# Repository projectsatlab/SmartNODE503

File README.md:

# SmartezNODE503
Smart ezNODE 503 hardware and software platform.

Hardware design assembly into 503 electric plant box based on ESP8266-012F WIFI module. 

Software architecture designed to interface TINKER MODE IoT devices platform.

Coming soon...

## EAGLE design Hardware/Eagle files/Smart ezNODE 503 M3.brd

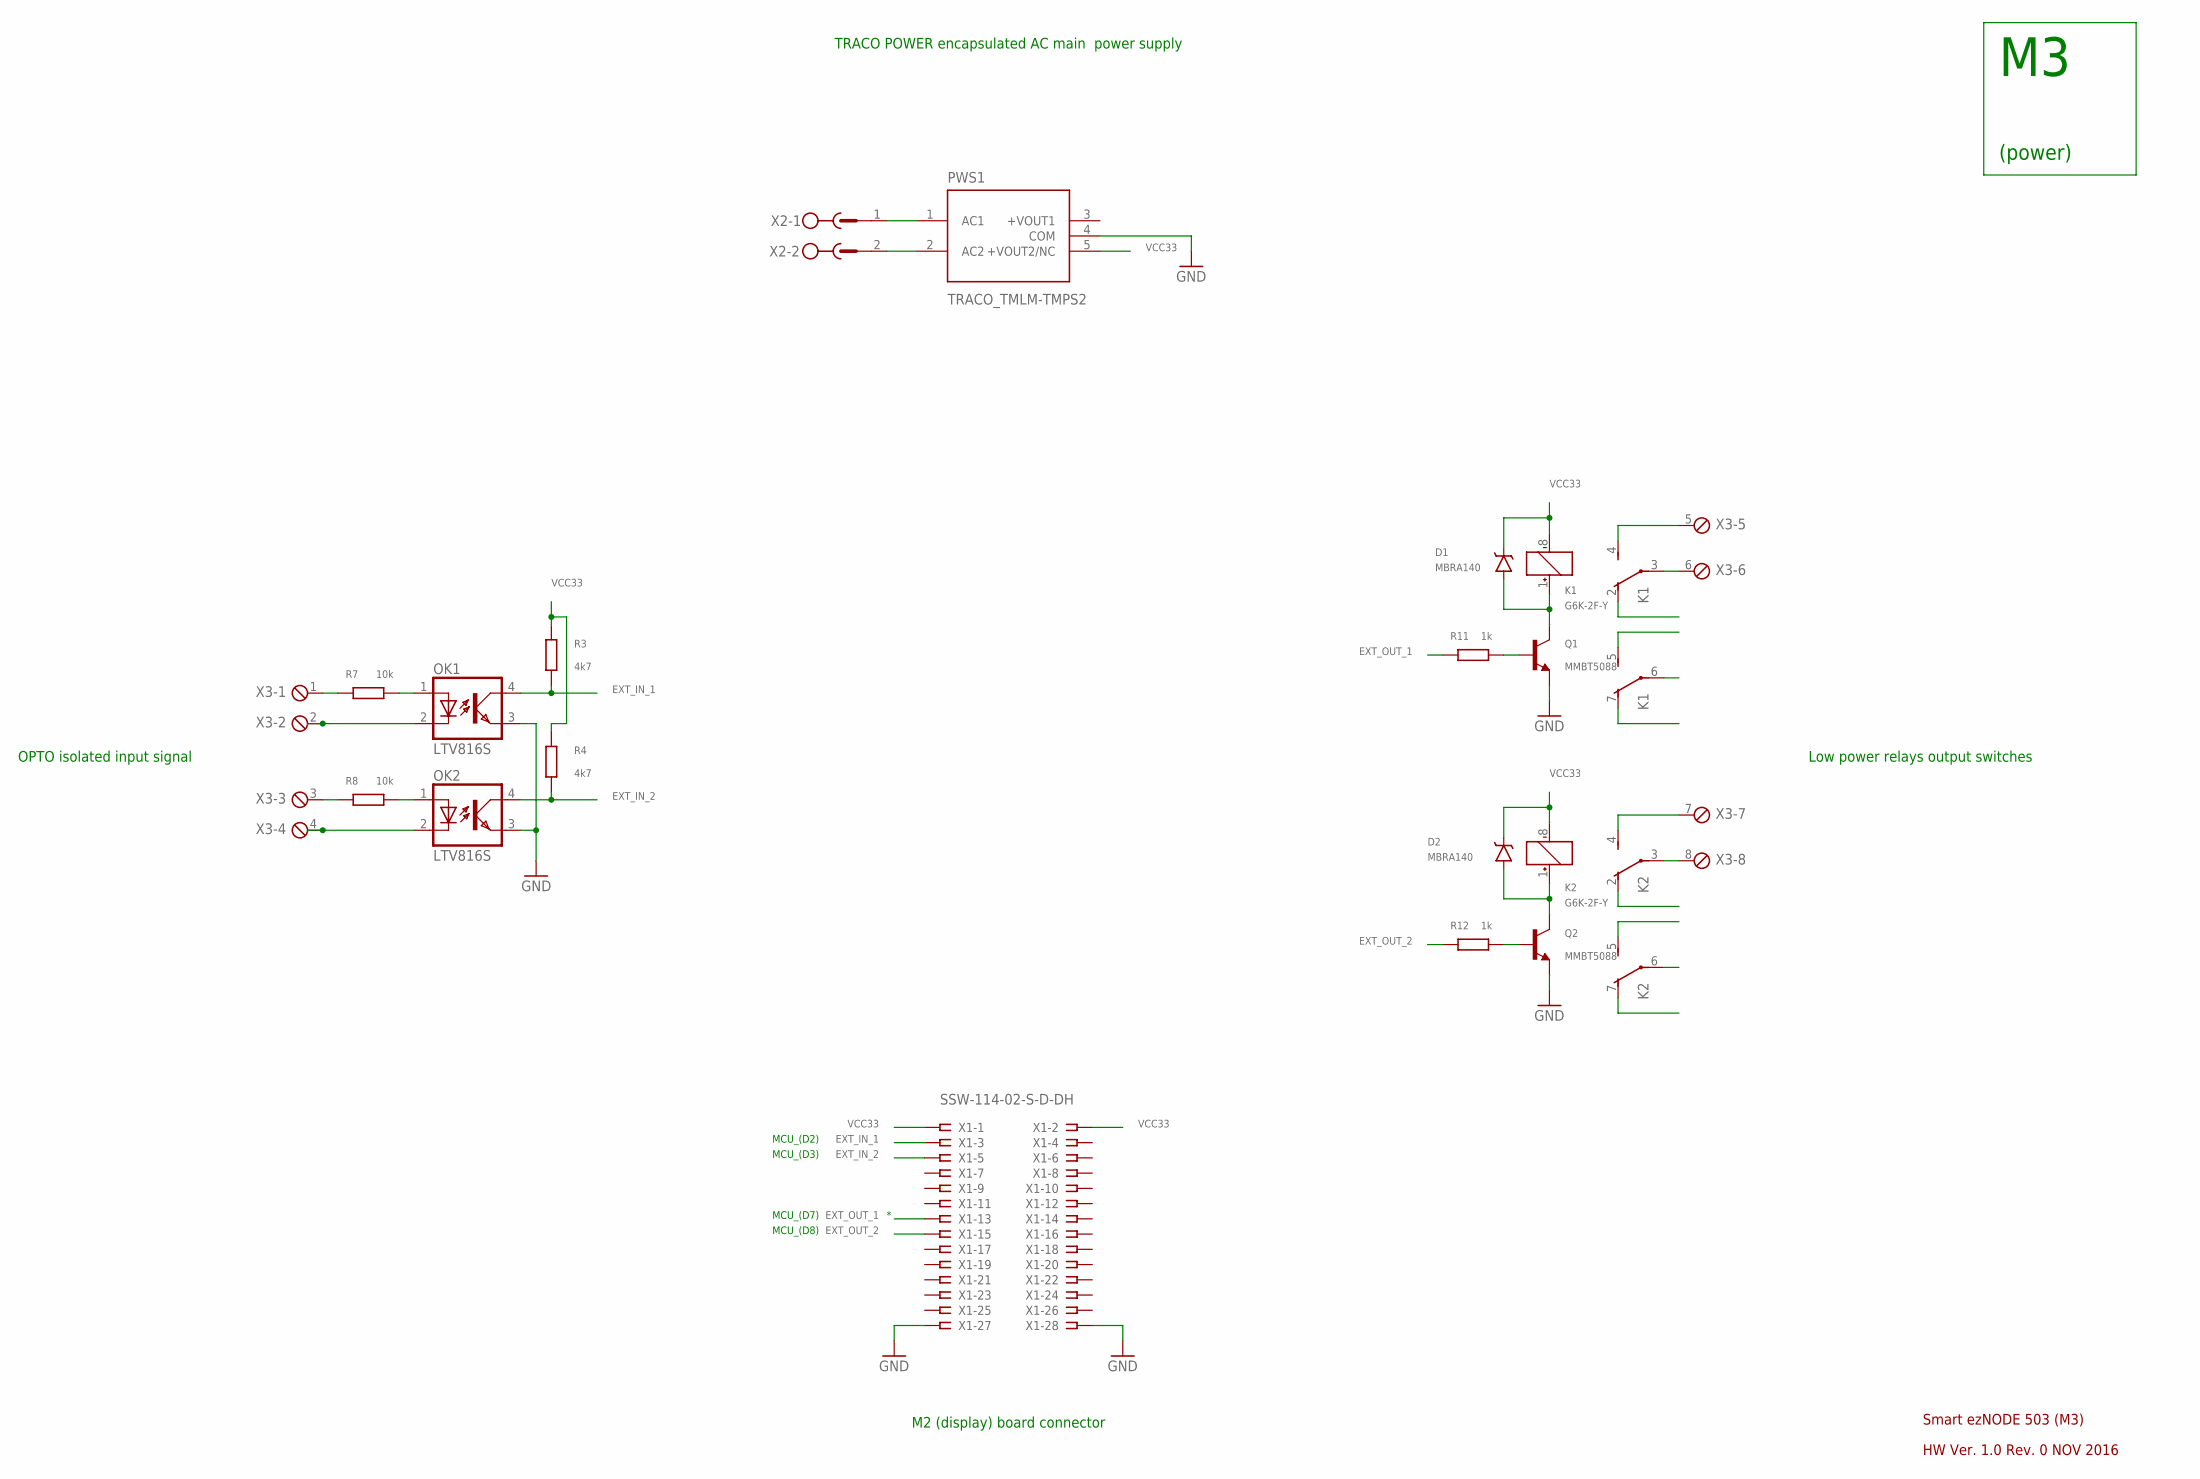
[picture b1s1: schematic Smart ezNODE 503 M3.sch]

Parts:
D1, D2: MBRA140; SMA-DIODE
K1, K2: G6K-2F-Y
OK1, OK2: LTV816S; SMD4
PWS1: TRACO_TMLM-TMPS2; TRACO_TMPS03XXX
Q1, Q2: MMBT5088; SOT23-3
R3, R4: 4k7; R0402
R7, R8: 10k; R0402
R11, R12: 1k; R0402
X1: SSW-114-02-S-D-DH; FTE-114-XX-G-DH
X2: MSTBV2
X3: MPT8; 8POL254

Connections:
EXT_IN_1: OK1.4 (COL), R3.1, X1.3
EXT_IN_2: OK2.4 (COL), R4.1, X1.5
EXT_OUT_1: R11.1, X1.13
EXT_OUT_2: R12.1, X1.15
GND: OK1.3 (EMIT), OK2.3 (EMIT), PWS1.4 (COM), Q1.2 (E), Q2.2 (E), X1.27, X1.28
unnamed: PWS1.1 (AC1), X2.1
unnamed: PWS1.2 (AC2), X2.2
unnamed: R7.1, X3.1
unnamed: R8.1, X3.3
unnamed: K1.4 (S), X3.5
unnamed: OK1.2 (C), X3.2
unnamed: OK1.1 (A), R7.2
unnamed: OK2.1 (A), R8.2
unnamed: OK2.2 (C), X3.4
unnamed: K1.3, X3.6
unnamed: D1.A, K1.1 (+), Q1.3 (C)
unnamed: D2.A, K2.1 (+), Q2.3 (C)
unnamed: Q1.1 (B), R11.2
unnamed: Q2.1 (B), R12.2
unnamed: K2.4 (S), X3.7
unnamed: K2.3, X3.8
VCC33: D1.C, D2.C, K1.8 (-), K2.8 (-), PWS1.5 (+VOUT2/NC), R3.2, R4.2, X1.1, X1.2

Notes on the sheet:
(power)
Smart ezNODE 503 (M3)
HW Ver. 1.0 Rev. 0 NOV 2016
TRACO POWER encapsulated AC main power supply
MCU_(D2)
MCU_(D3)
MCU_(D7)
MCU_(D8)
OPTO isolated input signal
Low power relays output switches
M2 (display) board connector

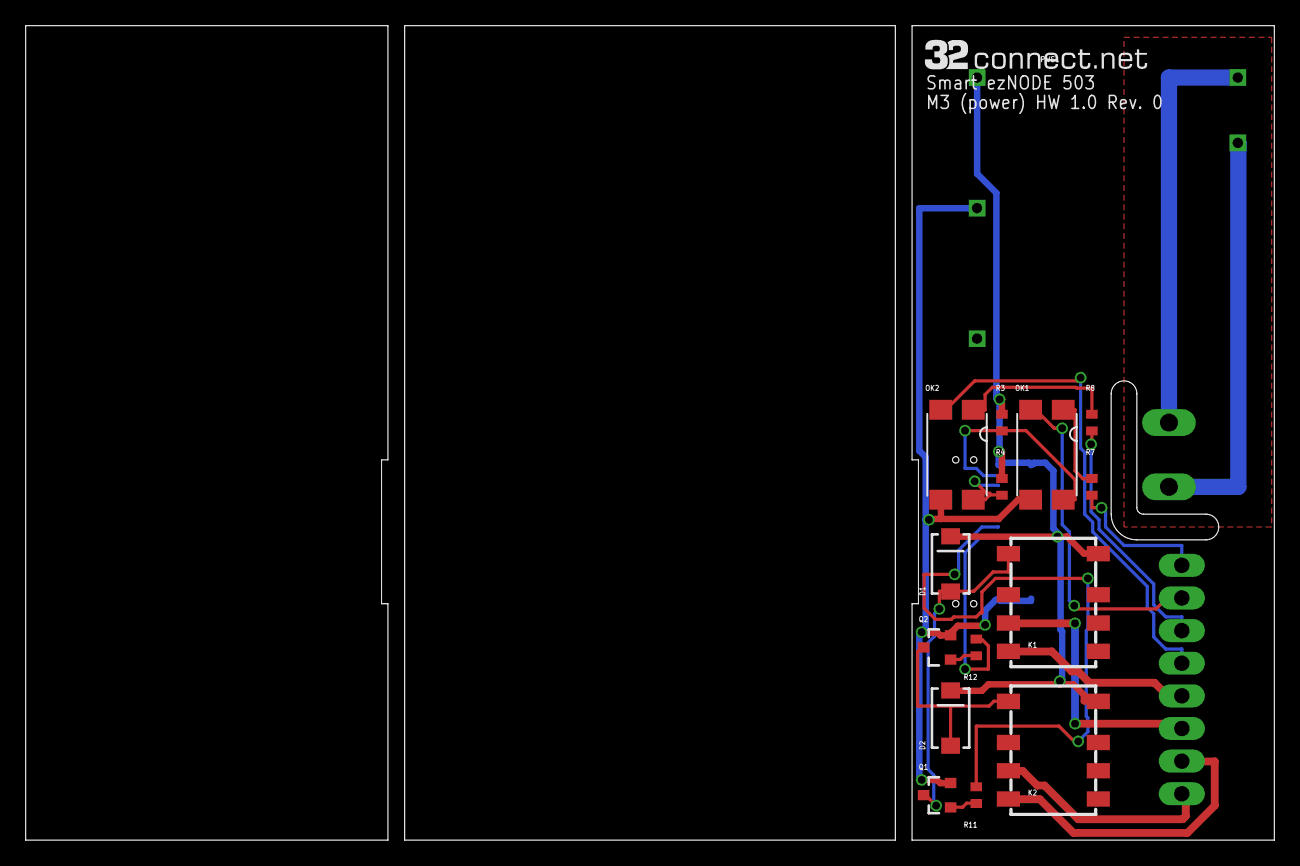
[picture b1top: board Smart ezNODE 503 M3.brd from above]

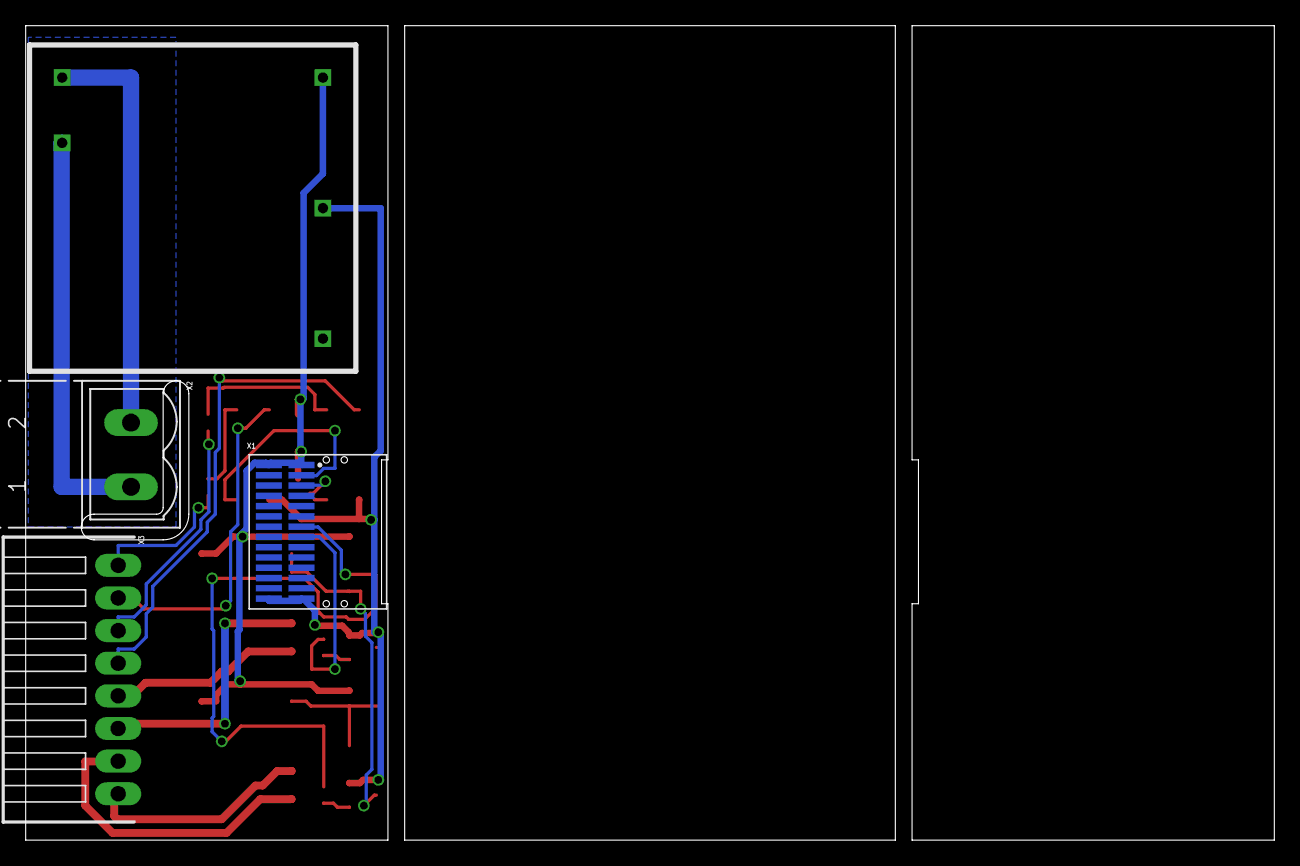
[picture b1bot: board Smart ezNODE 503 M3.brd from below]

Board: 2 copper layers, 97.2 x 63.4 mm, 18 parts (4 on the bottom side), 22 nets.

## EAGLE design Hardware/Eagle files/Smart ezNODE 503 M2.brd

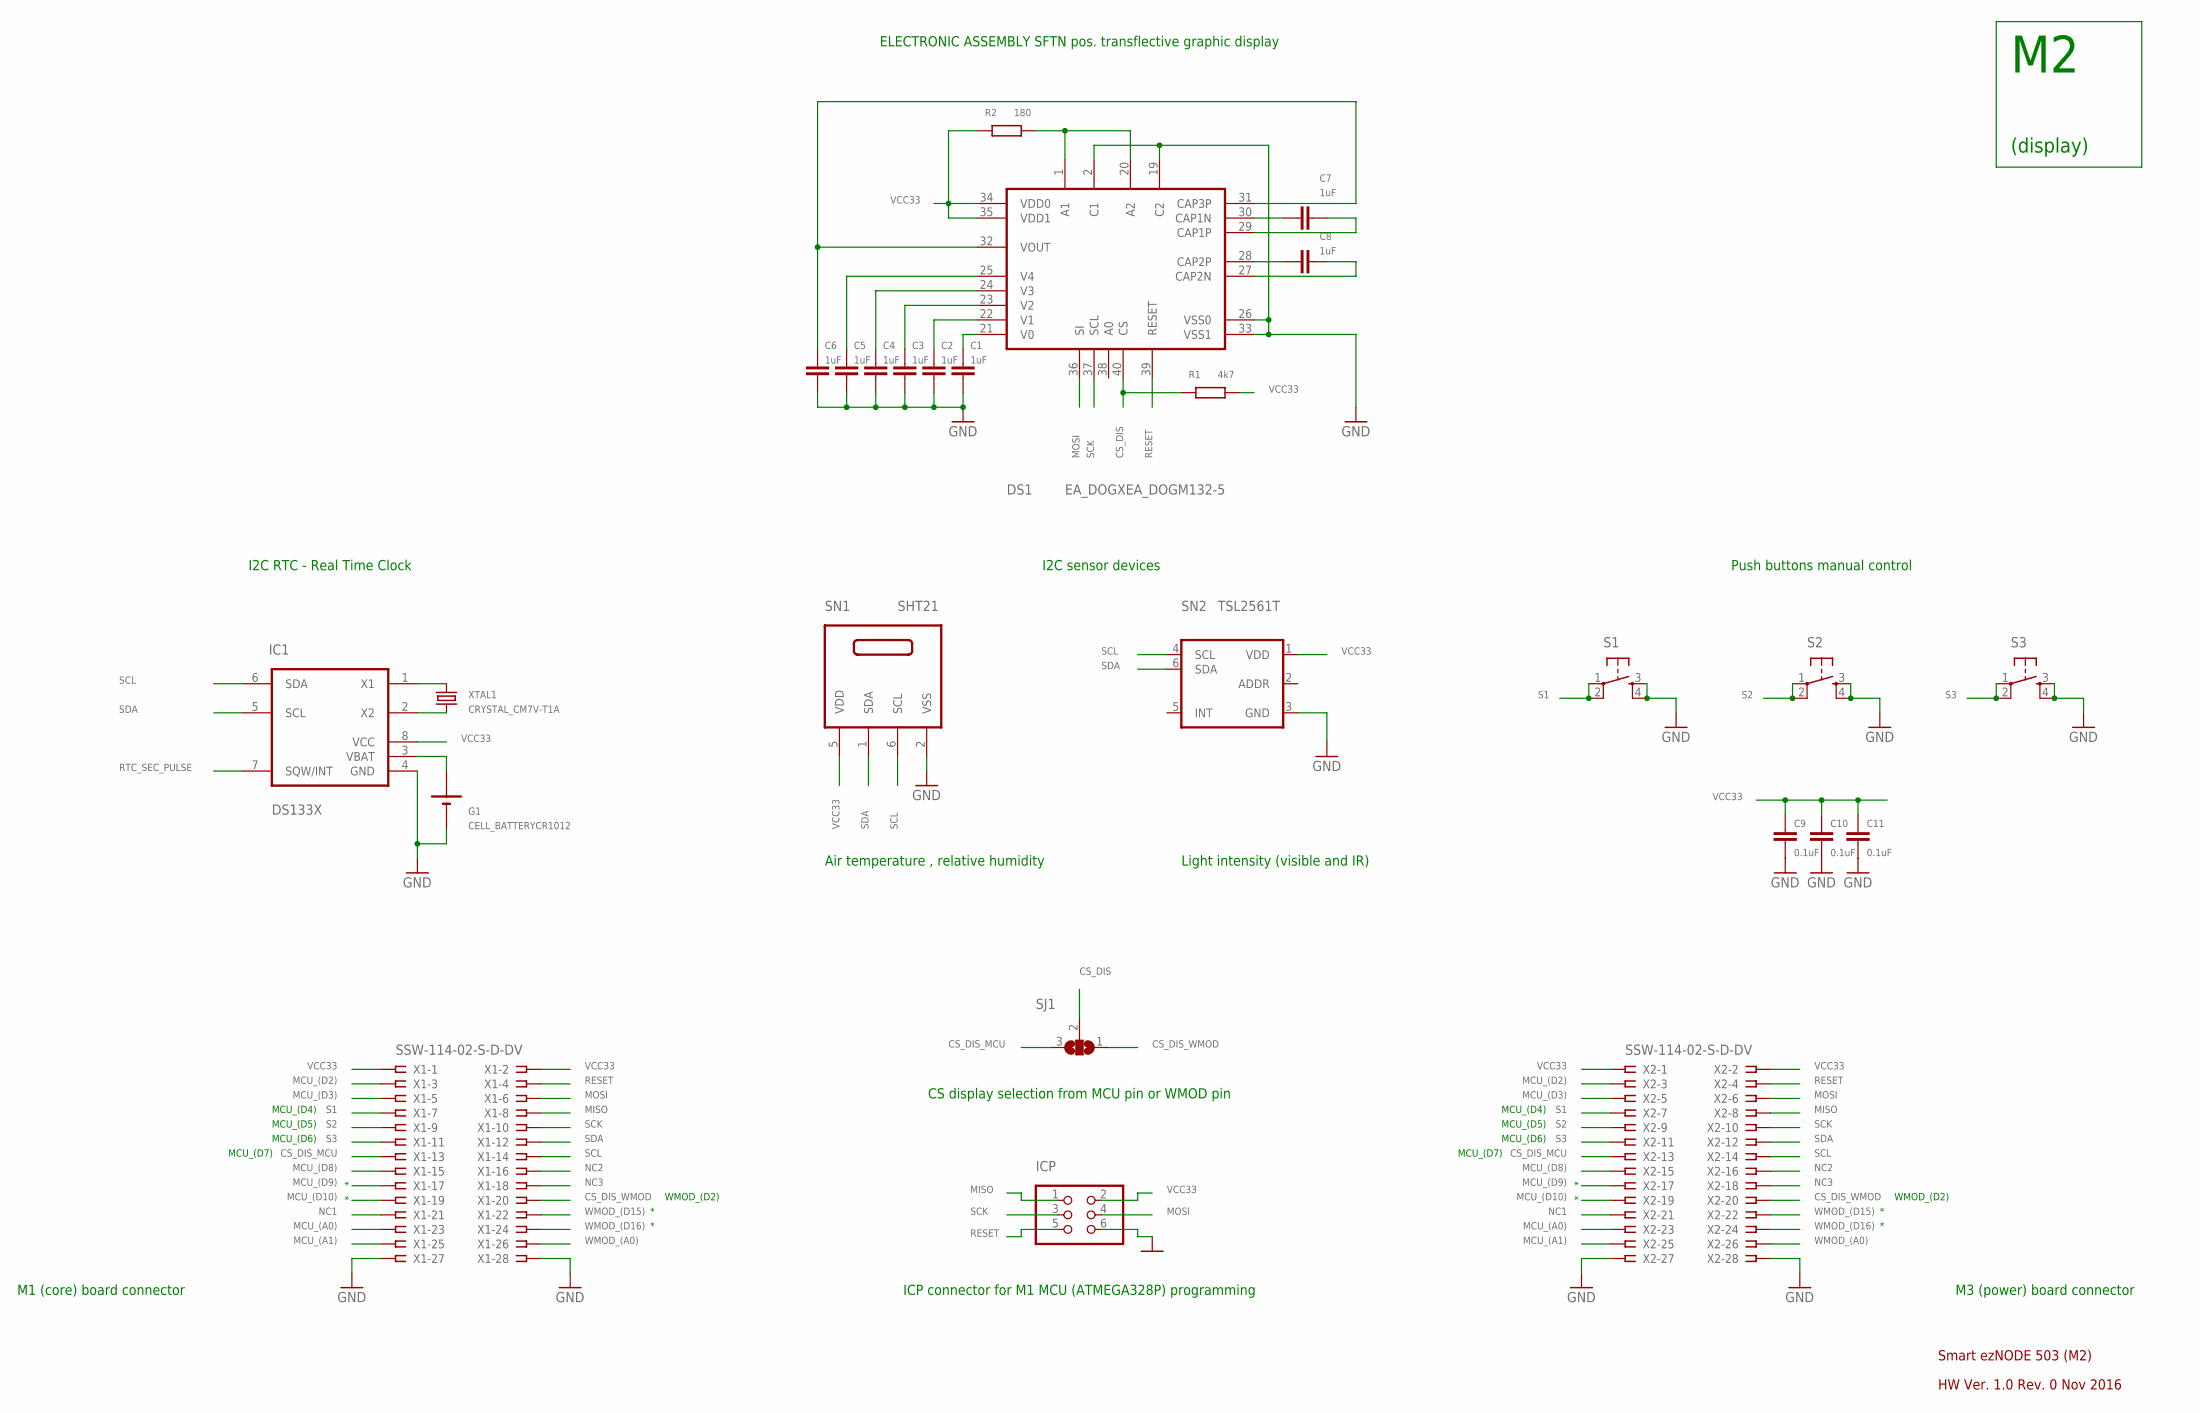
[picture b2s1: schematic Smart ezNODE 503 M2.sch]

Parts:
C1, C2, C3, C4, C5, C6, C7, C8: 1uF; C0402
C9, C10, C11: 0.1uF; C0402
DS1: EA_DOGXEA_DOGM132-5; EA_DOGM
G1: CELL_BATTERYCR1012; 12MM_SMD_COIN_CELL_BATTERY_HOLDER
IC1: DS133X; MICRO08
ICP: PINHD-2X3/SMD; 2X3_SMD
R1: 4k7; R0402
R2: 180; R0805
S1, S2, S3: TAC_SWITCH3; C&KKSCX_BEND
SJ1: SJ2W; SJ_2
SN1: SHT21; DFN6/SHT
SN2: TSL2561T; TMB-6
X1, X2: SSW-114-02-S-D-DV; CLE-114-01-X-DV-A
XTAL1: CRYSTAL_CM7V-T1A

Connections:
CS_DIS: DS1.40 (CS), R1.1, SJ1.2
CS_DIS_MCU: SJ1.3, X1.13, X2.13
CS_DIS_WMOD: SJ1.1, X1.20, X2.20
GND: C1.2, C2.2, C3.2, C4.2, C5.2, C6.2, C9.2, C10.2, C11.2, DS1.2 (C1), DS1.19 (C2), DS1.26 (VSS0), DS1.33 (VSS1), G1.P$2 (-), IC1.4 (GND), ICP.6, S1.3, S1.4, S2.3, S2.4, S3.3, S3.4, SN1.2 (VSS), SN2.3 (GND), X1.27, X1.28, X2.27, X2.28
MCU_(A0): X1.23, X2.23
MCU_(A1): X1.25, X2.25
MCU_(D2): X1.3, X2.3
MCU_(D3): X1.5, X2.5
MCU_(D8): X1.15, X2.15
MCU_(D9): X1.17, X2.17
MCU_(D10): X1.19, X2.19
MISO: ICP.1, X1.8, X2.8
MOSI: DS1.36 (SI), ICP.4, X1.6, X2.6
unnamed: IC1.1 (X1), XTAL1.P$2 (2)
unnamed: IC1.2 (X2), XTAL1.P$1 (1)
unnamed: DS1.1 (A1), DS1.20 (A2), R2.1
unnamed: C1.1, DS1.21 (V0)
unnamed: C7.1, DS1.30 (CAP1N)
unnamed: C2.1, DS1.22 (V1)
unnamed: C3.1, DS1.23 (V2)
unnamed: C4.1, DS1.24 (V3)
unnamed: C5.1, DS1.25 (V4)
unnamed: C6.1, DS1.31 (CAP3P), DS1.32 (VOUT)
unnamed: C7.2, DS1.29 (CAP1P)
unnamed: C8.1, DS1.28 (CAP2P)
unnamed: C8.2, DS1.27 (CAP2N)
unnamed: G1.P$1 (+), IC1.3 (VBAT)
NC1: X1.21, X2.21
NC2: X1.16, X2.16
NC3: X1.18, X2.18
RESET: DS1.39 (RESET), ICP.5, X1.4, X2.4
RTC_SEC_PULSE: IC1.7 (SQW/INT)
S1: S1.1, S1.2, X1.7, X2.7
S2: S2.1, S2.2, X1.9, X2.9
S3: S3.1, S3.2, X1.11, X2.11
SCK: DS1.37 (SCL), ICP.3, X1.10, X2.10
SCL: IC1.5 (SCL), SN1.6 (SCL), SN2.4 (SCL), X1.14, X2.14
SDA: IC1.6 (SDA), SN1.1 (SDA), SN2.6 (SDA), X1.12, X2.12
VCC33: C9.1, C10.1, C11.1, DS1.34 (VDD0), DS1.35 (VDD1), IC1.8 (VCC), ICP.2, R1.2, R2.2, SN1.5 (VDD), SN2.1 (VDD), X1.1, X1.2, X2.1, X2.2
WMOD_(A0): X1.26, X2.26
WMOD_(D15): X1.22, X2.22
WMOD_(D16): X1.24, X2.24

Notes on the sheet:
(display)
Smart ezNODE 503 (M2)
HW Ver. 1.0 Rev. 0 Nov 2016
WMOD_(D2)
MCU_(D4)
MCU_(D5)
MCU_(D6)
ELECTRONIC ASSEMBLY SFTN pos. transflective graphic display
I2C sensor devices
Air temperature , relative humidity
Light intensity (visible and IR)
I2C RTC - Real Time Clock
ICP connector for M1 MCU (ATMEGA328P) programming
M1 (core) board connector
M3 (power) board connector
Push buttons manual control
MCU_(D7)
CS display selection from MCU pin or WMOD pin

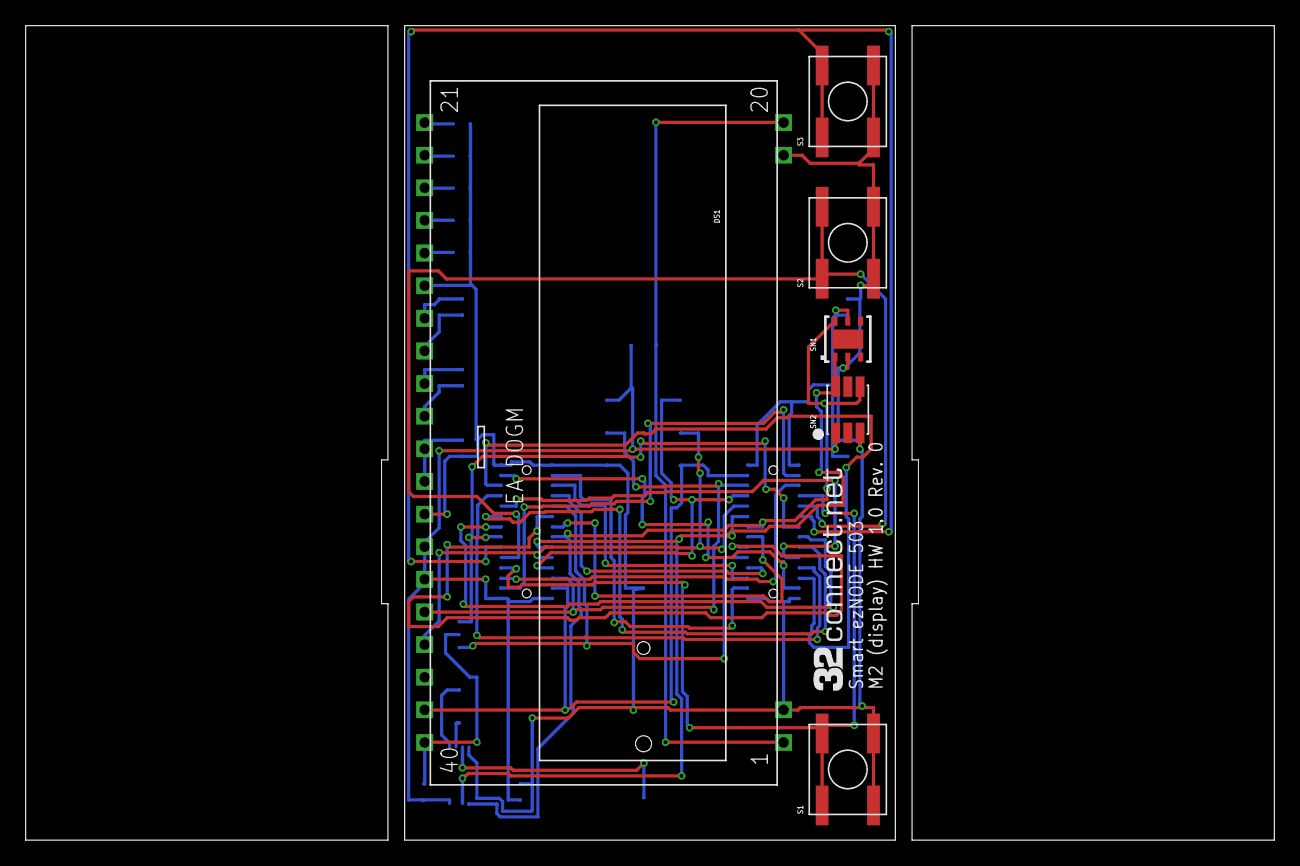
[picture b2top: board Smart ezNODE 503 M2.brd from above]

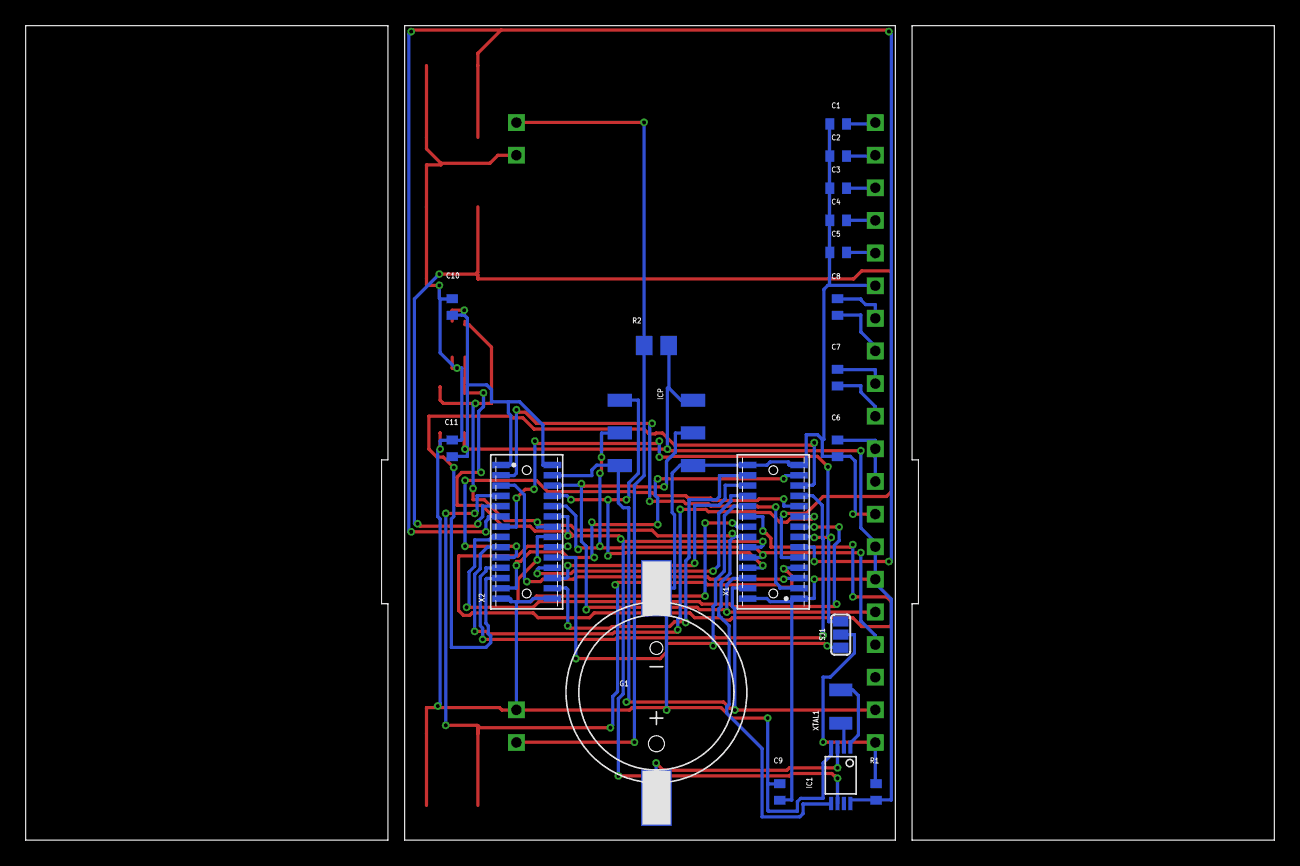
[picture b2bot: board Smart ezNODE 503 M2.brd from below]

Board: 2 copper layers, 97.2 x 63.4 mm, 26 parts (20 on the bottom side), 41 nets.

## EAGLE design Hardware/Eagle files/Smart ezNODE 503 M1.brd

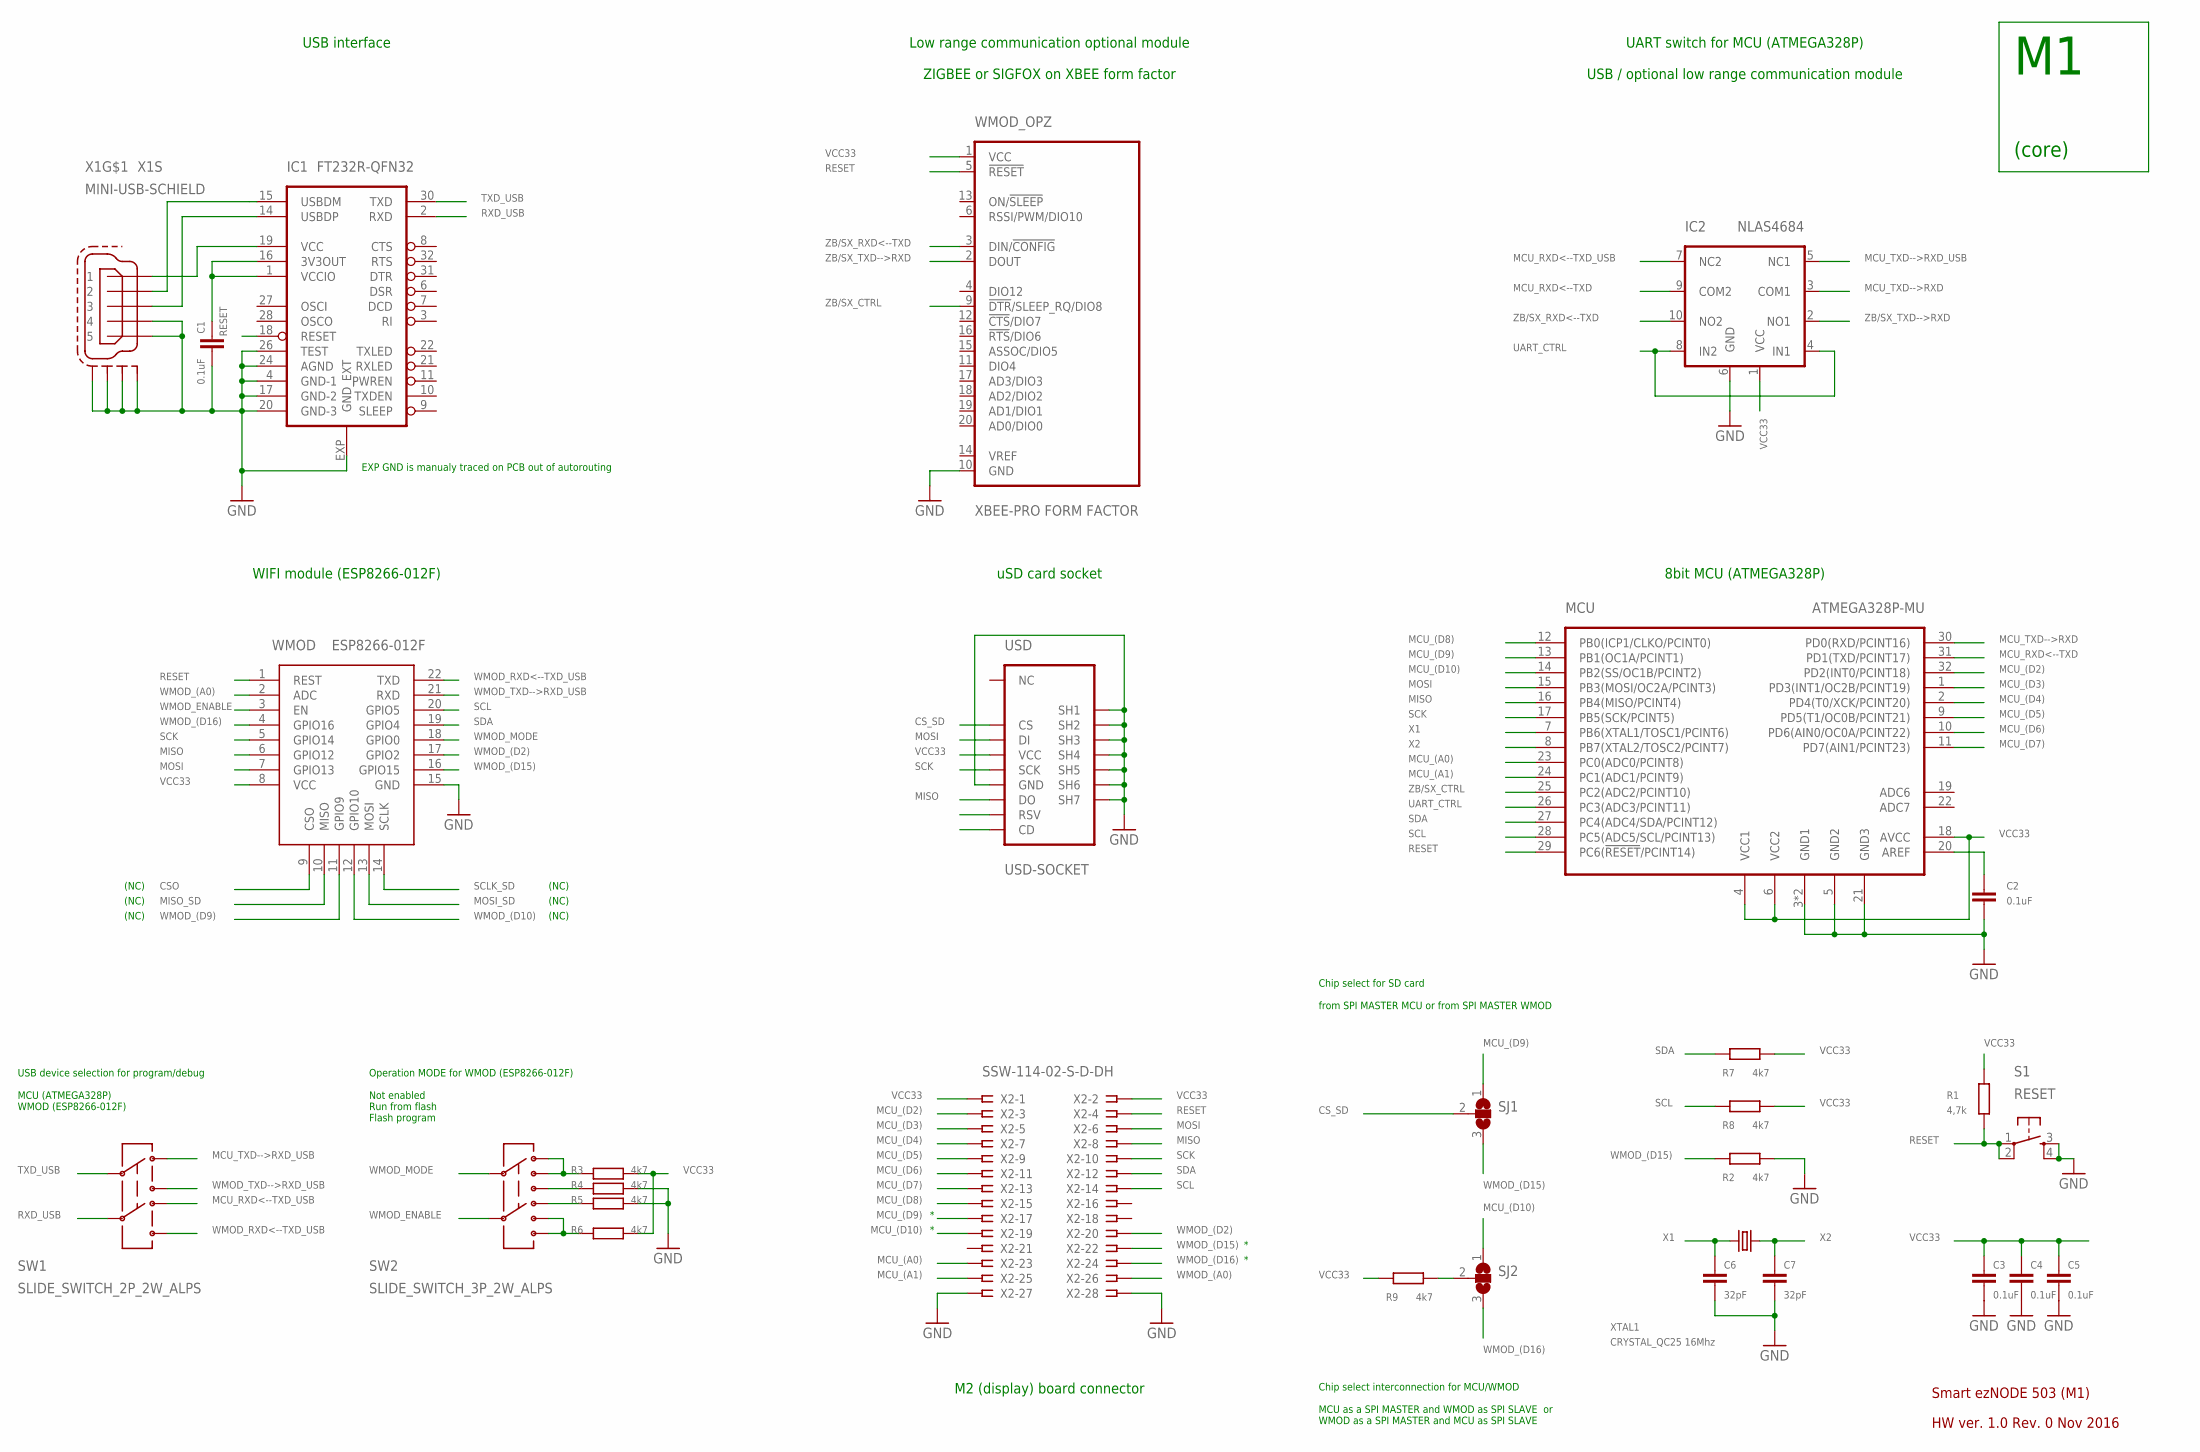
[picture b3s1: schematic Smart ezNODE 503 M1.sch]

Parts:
C1, C2, C3, C4, C5: 0.1uF; C0402
C6, C7: 32pF; C0201
IC1: FT232R-QFN32; QFN32
IC2: NLAS4684; MSOP10
MCU: ATMEGA328P-MU; MLF32
R1: 4,7k; R0402
R2, R3, R4, R5, R6, R7, R8, R9: 4k7; R0402
S1: RESET; C&K_KMS
SJ1, SJ2: SJ2W; SJ_2
SW1: SLIDE_SWITCH_2P_2W_ALPS; SLIDE_SWITCH_ALPS_SSSS820201
SW2: SLIDE_SWITCH_3P_2W_ALPS; SLIDE_SWITCH_ALPS_SSSS820301
USD: USD-SOCKET; USD-SOCKET-PP
WMOD: ESP8266-012F; ESP8266-ESP12
WMOD_OPZ: XBEE-PRO FORM FACTOR; XBEE-PRO
X1: MINI-USB-SCHIELD; MOLEX_67503-X20
X2: SSW-114-02-S-D-DH; FTE-114-XX-G-DH
XTAL1: CRYSTAL_QC25 16Mhz; CRYSTAL_QC25

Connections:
CSO: WMOD.9 (CSO)
CS_SD: SJ1.2, USD.P$2 (CS)
D+: IC1.14 (USBDP), X1.3
D-: IC1.15 (USBDM), X1.2
GND: C1.2, C2.2, C3.2, C4.2, C5.2, C6.2, C7.2, IC1.4 (GND-1), IC1.17 (GND-2), IC1.20 (GND-3), IC1.24 (AGND), IC1.26 (TEST), IC1.EXP (GND_EXT), IC2.6 (GND), MCU.3 (GND1), MCU.5 (GND2), MCU.21 (GND3), MCU.TH (GND1), R2.2, R4.1, R5.1, S1.3, S1.4, USD.P$6 (GND), USD.P$9 (SH1), USD.P$10 (SH2), USD.P$12 (SH3), USD.P$13 (SH4), USD.P$14 (SH5), USD.P$15 (SH6), USD.P$16 (SH7), WMOD.15 (GND), WMOD_OPZ.10 (GND), X1.4, X1.5, X1.M1 (S1), X1.M2 (S2), X1.M3 (S3), X1.M4 (S4), X2.27, X2.28
MCU_(A0): MCU.23 (PC0(ADC0/PCINT8)), X2.23
MCU_(A1): MCU.24 (PC1(ADC1/PCINT9)), X2.25
MCU_(D2): MCU.32 (PD2(INT0/PCINT18)), X2.3
MCU_(D3): MCU.1 (PD3(INT1/OC2B/PCINT19)), X2.5
MCU_(D4): MCU.2 (PD4(T0/XCK/PCINT20)), X2.7
MCU_(D5): MCU.9 (PD5(T1/OC0B/PCINT21)), X2.9
MCU_(D6): MCU.10 (PD6(AIN0/OC0A/PCINT22)), X2.11
MCU_(D7): MCU.11 (PD7(AIN1/PCINT23)), X2.13
MCU_(D8): MCU.12 (PB0(ICP1/CLKO/PCINT0)), X2.15
MCU_(D9): MCU.13 (PB1(OC1A/PCINT1)), SJ1.1, X2.17
MCU_(D10): MCU.14 (PB2(SS/OC1B/PCINT2)), SJ2.1, X2.19
MCU_RXD<--TXD: IC2.9 (COM2), MCU.31 (PD1(TXD/PCINT17))
MCU_RXD<--TXD_USB: IC2.7 (NC2), SW1.4
MCU_TXD-->RXD: IC2.3 (COM1), MCU.30 (PD0(RXD/PCINT16))
MCU_TXD-->RXD_USB: IC2.5 (NC1), SW1.1
MISO: MCU.16 (PB4(MISO/PCINT4)), USD.P$7 (DO), WMOD.6 (GPIO12), X2.8
MISO_SD: WMOD.10 (MISO)
MOSI: MCU.15 (PB3(MOSI/OC2A/PCINT3)), USD.P$3 (DI), WMOD.7 (GPIO13), X2.6
MOSI_SD: WMOD.13 (MOSI)
unnamed: R9.2, SJ2.2
unnamed: C1.1, IC1.1 (VCCIO), IC1.16 (3V3OUT)
unnamed: R6.2, SW2.6, SW2.8
unnamed: C2.1, MCU.20 (AREF)
unnamed: R3.2, SW2.1, SW2.2
unnamed: R4.2, SW2.4
unnamed: R5.2, SW2.5
RESET: IC1.18 (RESET), MCU.29 (PC6(!RESET!/PCINT14)), R1.1, S1.1, S1.2, WMOD.1 (REST), WMOD_OPZ.5 (!RESET), X2.4
RXD_USB: IC1.2 (RXD), SW1.5
SCK: MCU.17 (PB5(SCK/PCINT5)), USD.P$5 (SCK), WMOD.5 (GPIO14), X2.10
SCL: MCU.28 (PC5(ADC5/SCL/PCINT13)), R8.1, WMOD.20 (GPIO5), X2.14
SCLK_SD: WMOD.14 (SCLK)
SDA: MCU.27 (PC4(ADC4/SDA/PCINT12)), R7.1, WMOD.19 (GPIO4), X2.12
TXD_USB: IC1.30 (TXD), SW1.2
UART_CTRL: IC2.4 (IN1), IC2.8 (IN2), MCU.26 (PC3(ADC3/PCINT11))
VBUS: IC1.19 (VCC), X1.1
VCC33: C3.1, C4.1, C5.1, IC2.1 (VCC), MCU.4 (VCC1), MCU.6 (VCC2), MCU.18 (AVCC), R1.2, R3.1, R6.1, R7.2, R8.2, R9.1, USD.P$4 (VCC), WMOD.8 (VCC), WMOD_OPZ.1 (VCC), X2.1, X2.2
WMOD_(A0): WMOD.2 (ADC), X2.26
WMOD_(D2): WMOD.17 (GPIO2), X2.20
WMOD_(D9): WMOD.11 (GPIO9)
WMOD_(D10): WMOD.12 (GPIO10)
WMOD_(D15): R2.1, SJ1.3, WMOD.16 (GPIO15), X2.22
WMOD_(D16): SJ2.3, WMOD.4 (GPIO16), X2.24
WMOD_ENABLE: SW2.7, WMOD.3 (EN)
WMOD_MODE: SW2.3, WMOD.18 (GPIO0)
WMOD_RXD<--TXD_USB: SW1.6, WMOD.22 (TXD)
WMOD_TXD-->RXD_USB: SW1.3, WMOD.21 (RXD)
X1: C6.1, MCU.7 (PB6(XTAL1/TOSC1/PCINT6)), XTAL1.P$1 (1)
X2: C7.1, MCU.8 (PB7(XTAL2/TOSC2/PCINT7)), XTAL1.P$3 (3)
ZB/SX_CTRL: MCU.25 (PC2(ADC2/PCINT10)), WMOD_OPZ.9 (!DTR!/SLEEP_RQ/DIO8)
ZB/SX_RXD<--TXD: IC2.10 (NO2), WMOD_OPZ.3 (DIN/!CONFIG)
ZB/SX_TXD-->RXD: IC2.2 (NO1), WMOD_OPZ.2 (DOUT)

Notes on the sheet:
Smart ezNODE 503 (M1)
HW ver. 1.0 Rev. 0 Nov 2016
(core)
Chip select for SD card from SPI MASTER MCU or from SPI MASTER WMOD
Chip select interconnection for MCU/WMOD MCU as a SPI MASTER and WMOD as SPI SLAVE or WMOD as a SPI MASTER and MCU as SPI SLAVE
USB device selection for program/debug MCU (ATMEGA328P) WMOD (ESP8266-012F)
Operation MODE for WMOD (ESP8266-012F) Not enabled Run from flash Flash program
Low range communication optional module ZIGBEE or SIGFOX on XBEE form factor
USB interface
UART switch for MCU (ATMEGA328P) USB / optional low range communication module
WIFI module (ESP8266-012F)
uSD card socket
8bit MCU (ATMEGA328P)
M2 (display) board connector
(NC)
EXP GND is manualy traced on PCB out of autorouting

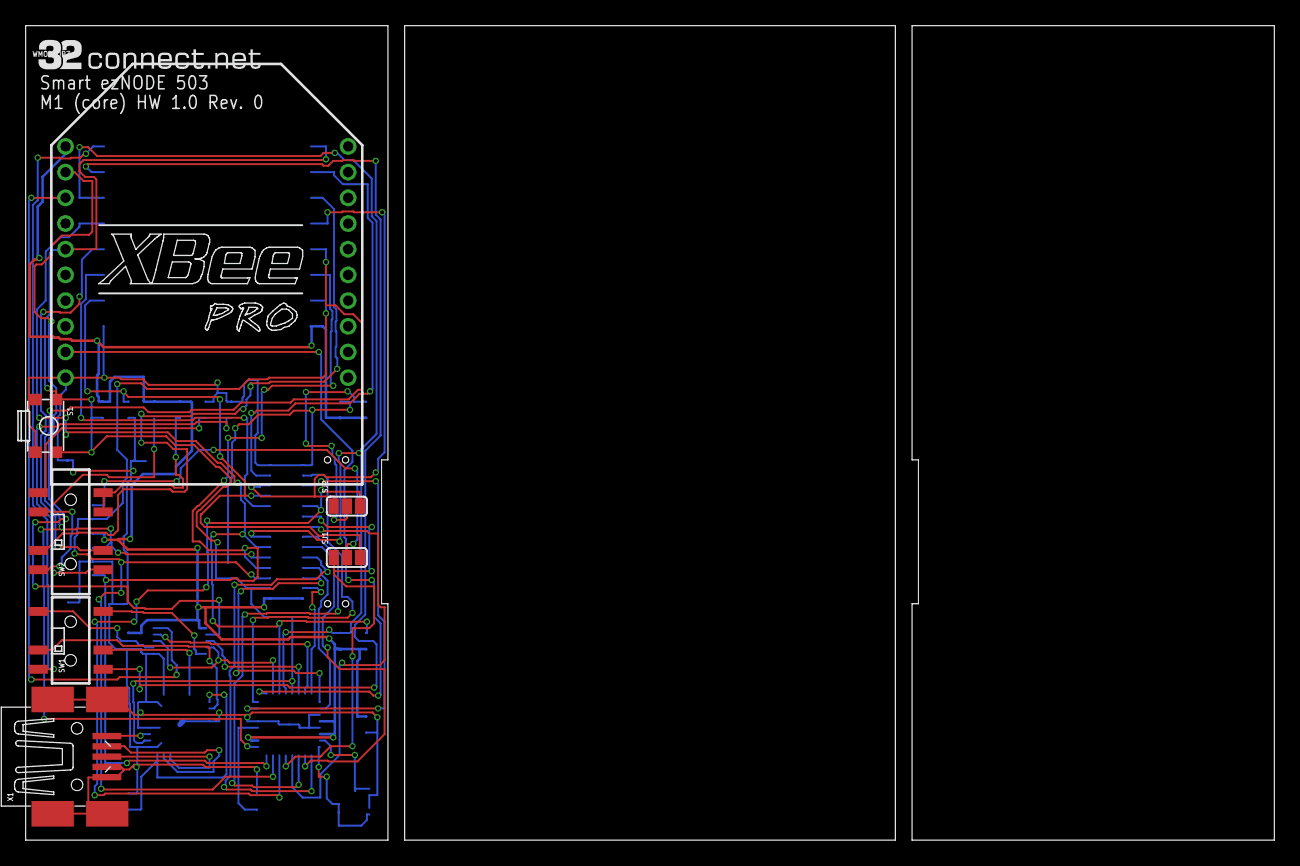
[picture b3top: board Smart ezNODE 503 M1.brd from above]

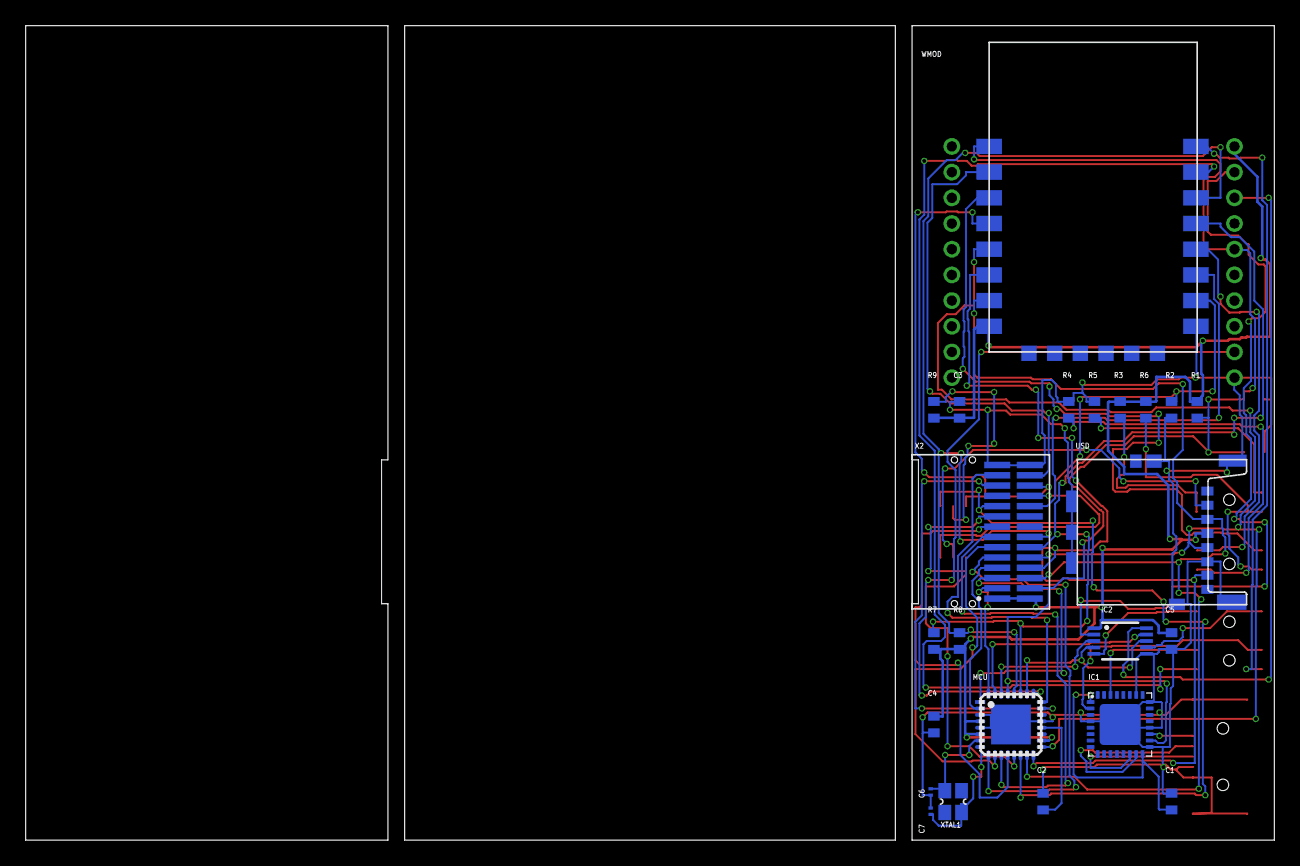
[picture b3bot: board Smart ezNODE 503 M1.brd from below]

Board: 2 copper layers, 97.2 x 63.4 mm, 30 parts (23 on the bottom side), 50 nets.

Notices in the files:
parts and their libraries:
SparkFun-Aesthetics: Licensing: Creative Commons ShareAlike 4.0 International - https://creativecommons.org/licenses/by-sa/4.0
sensirion: Copyright (C) 2011, Bob Starr
